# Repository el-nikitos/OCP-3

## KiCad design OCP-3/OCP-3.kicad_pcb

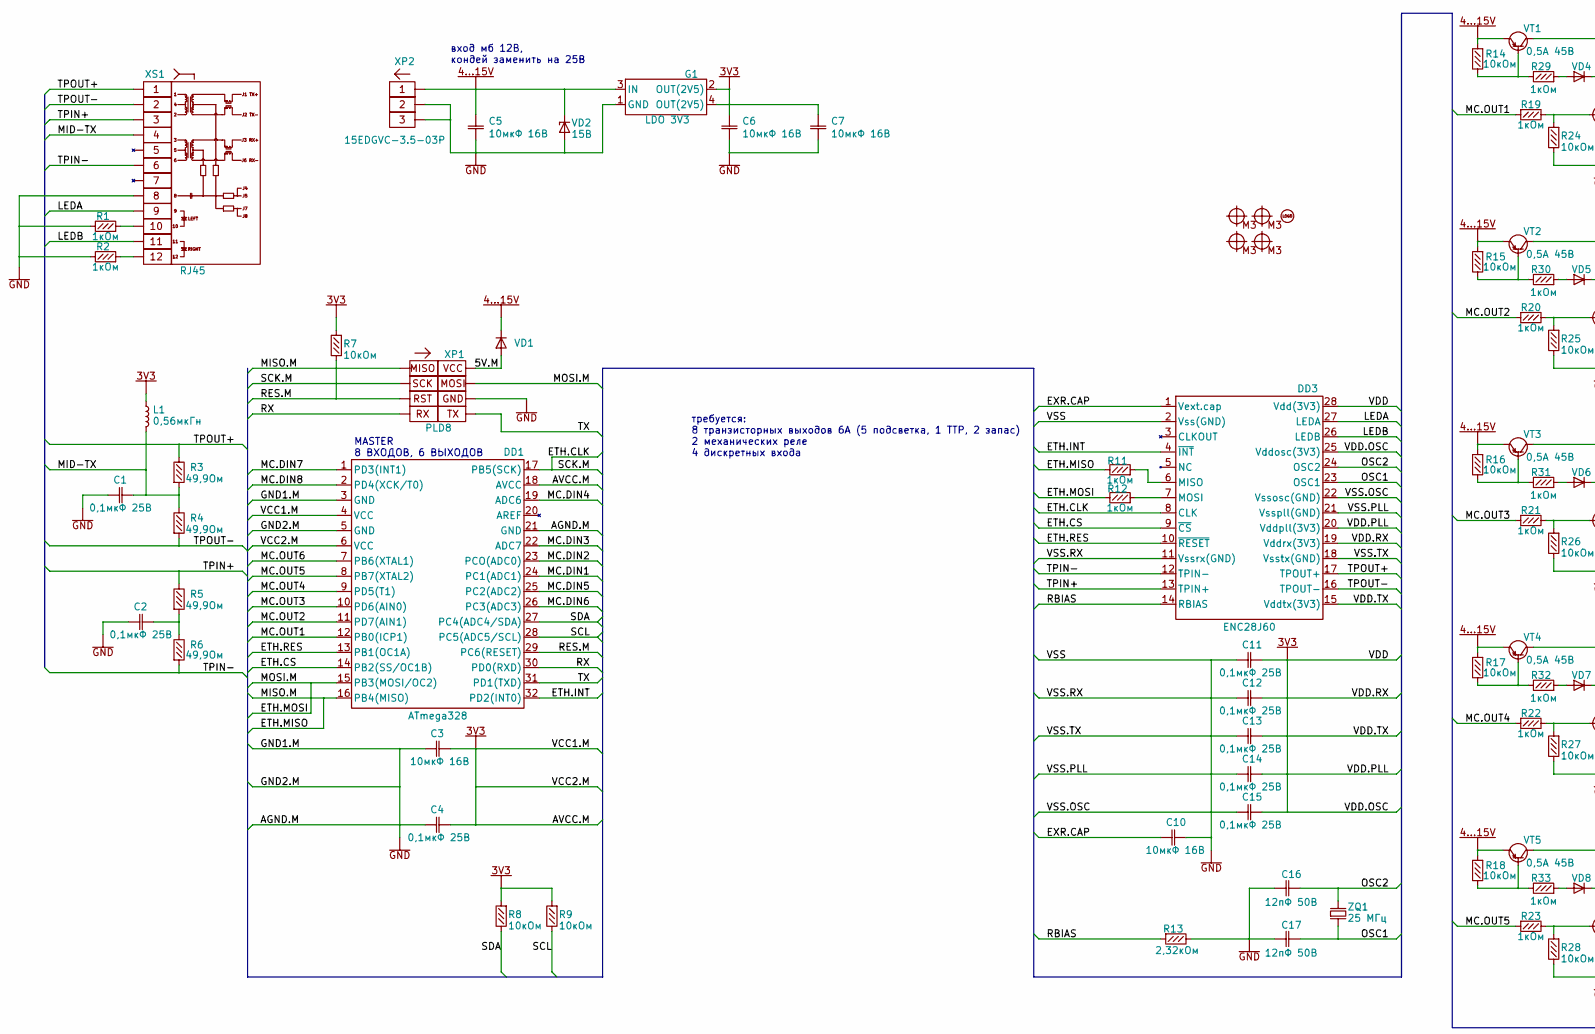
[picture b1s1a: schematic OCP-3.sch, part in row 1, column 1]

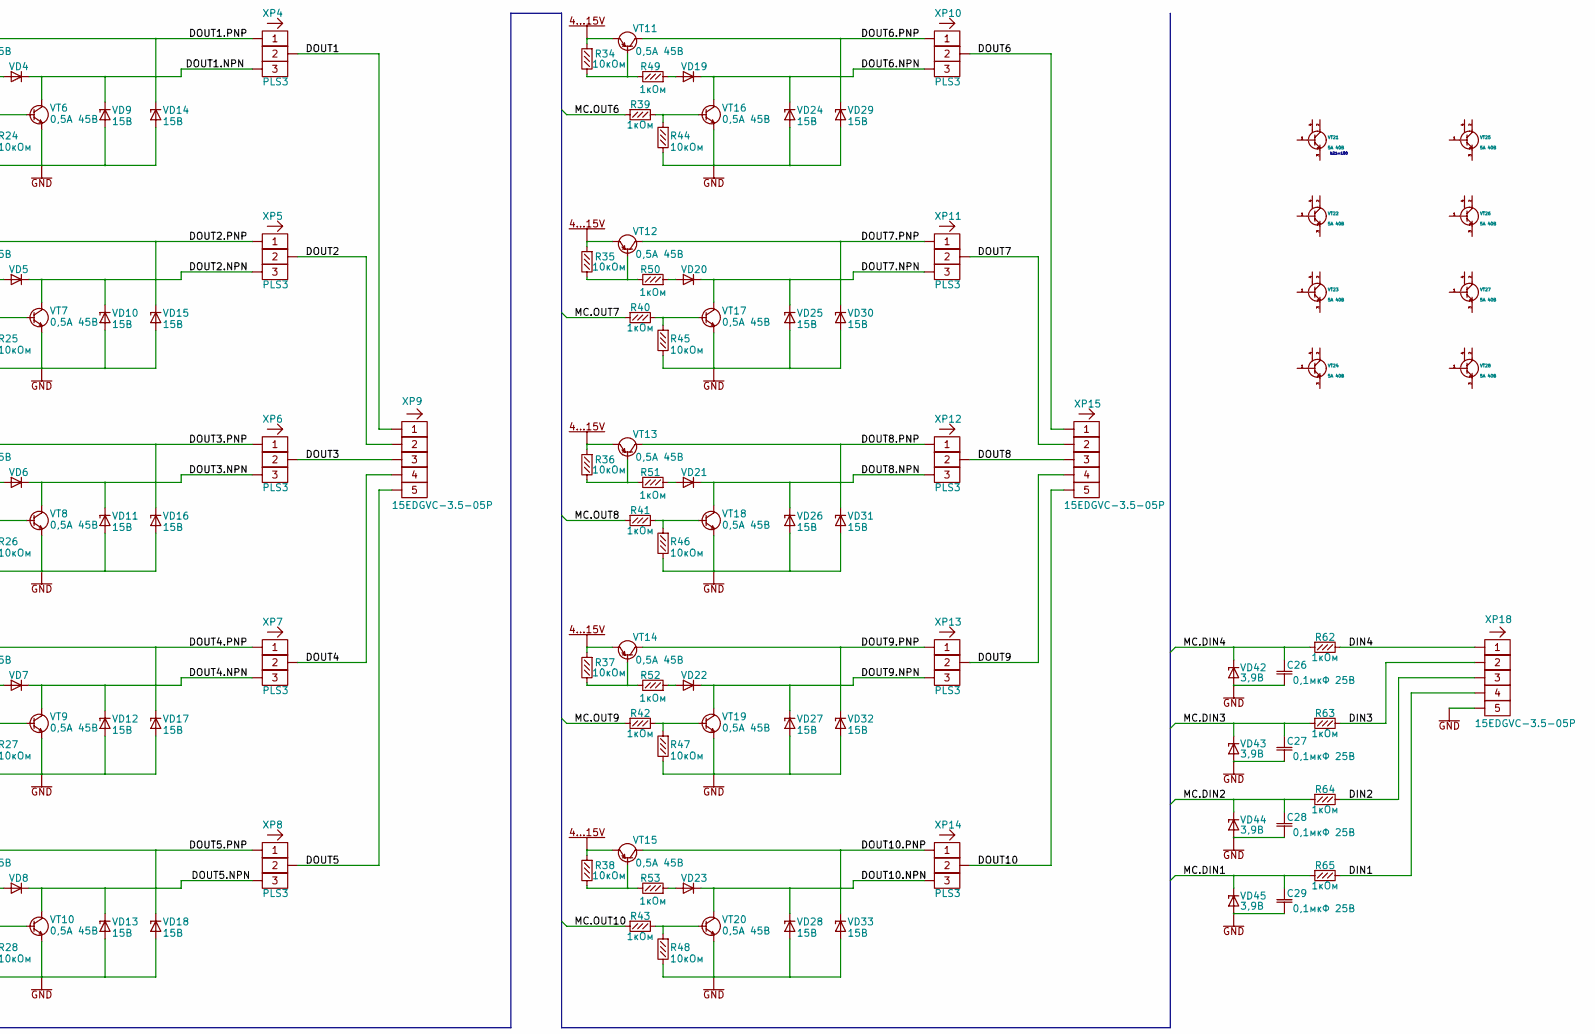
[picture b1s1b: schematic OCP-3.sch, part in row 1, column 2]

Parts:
C1, C2, C4, C11, C12, C13, C14, C15, C26, C27, C28, C29: Конденсатор*0,1мкФ*25В*0603; Конденсатор_SMD_IEC_0603
C3, C5, C6, C7, C10: Конденсатор*10мкФ*16В*0805; Конденсатор_SMD_IEC_0805
C16, C17: Конденсатор*12пФ*50В*0603; Конденсатор_SMD_IEC_0603
DD1: МК*ATmega168*TQFP32; микросхема_ATMEGA-8-161AU
DD3: Преобразователь*ETH-SPI*SSOP28; SSOP-28
G1: LDO*вход_18Вmax*выход_3,3В*ток_1,2АSOT-223; Транзистор_NPN_SOT223_pnp
L1: Чип-индуктивность*0,56мкГн*150мА*0805; Резистор_SMD_IEC_0805_0,125_Вт
R1, R2, R11, R12, R19, R20, R21, R22, R23, R29, R30, R31, R32, R33, R39, R40, R41, R42, R43, R49, R50, R51, R52, R53, R62, R63, R64, R65: Резистор*1кОм*0603; Резистор_SMD_0603_0,065_Вт_pnp
R3, R4, R5, R6: Резистор*49,9кОм*0603; Резистор_SMD_0603_0,065_Вт_pnp
R7, R8, R9, R14, R15, R16, R17, R18, R24, R25, R26, R27, R28, R34, R35, R36, R37, R38, R44, R45, R46, R47, R48: Резистор*10кОм*0603; Резистор_SMD_0603_0,065_Вт_pnp
R13: Резистор*2,32кОм*0603; Резистор_SMD_0603_0,065_Вт_pnp
VD1, VD4, VD5, VD6, VD7, VD8, VD19, VD20, VD21, VD22, VD23: Диод*75В*0,2А*SOD-323; D_SOD-323_HandSoldering
VD2, VD9, VD10, VD11, VD12, VD13, VD14, VD15, VD16, VD17, VD18, VD24, VD25, VD26, VD27, VD28, VD29, VD30, VD31, VD32, VD33: Стабилитрон*15В*SOD80; SOD-80
VD42, VD43, VD44, VD45: Стабилитрон*3,9В*SOD80; SOD-80
VT1, VT2, VT3, VT4, VT5, VT11, VT12, VT13, VT14, VT15: Транзистор*pnp*0,5А*45В*SOT23; Корпус_КТ-46
VT6, VT7, VT8, VT9, VT10, VT16, VT17, VT18, VT19, VT20: Транзистор*npn*0,5А*45В*SOT23; Корпус_КТ-46
VT21, VT22, VT23, VT24, VT25, VT26, VT27, VT28: Транзистор_NPN_1Б-2(4)К-3Э_0; Транзистор_NPN_SOT223
X1, X2, X3, X4: ico*отверстие*М3; Отверстие_М3
X5: ico*LOGO_NIKITOS_10х10; ni_10x10
XP1: Вилка*PLD*8контактов*2ряда*вертикальная*AVR+UART; Вилка_PLD8_вертикальная_AB
XP2: Клеммник*шаг_3,5*3контактов*1ряд*вертикальная; Клеммник_15EDGVC-3.5-03P
XP4, XP5, XP6, XP7, XP8, XP10, XP11, XP12, XP13, XP14: Вилка*PLS*3контактов*1ряд*вертикальная; Вилка_PLS3_вертикальная
XP9, XP15, XP18: Клеммник*шаг_3,5*5контактов*1ряд*вертикальная; Клеммник_15EDGVC-3.5-05P
XS1: Розетка*ETH+трансформатор*8p8c; Розетка_ETH_KLS12-TL002
ZQ1: Резонатор*25МГц*HC-49U; Резонатор_РК456МДУ(DIP)

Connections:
3V3: C3.1, C4.1, C6.1, C7.1, C11.1, C12.1, C13.1, C14.1, C15.1, DD1.4 (VCC), DD1.6 (VCC), DD1.18 (AVCC), DD3.15 (Vddtx(3V3)), DD3.19 (Vddrx(3V3)), DD3.20 (Vddpll(3V3)), DD3.25 (Vddosc(3V3)), DD3.28 (Vdd(3V3)), G1.2 (OUT(2V5)), G1.4 (OUT(2V5)), L1.1, R7.1, R8.1, R9.1
4...15V: C5.1, G1.3 (IN), R14.1, R15.1, R16.1, R17.1, R18.1, R34.1, R35.1, R36.1, R37.1, R38.1, VD1.1, VD2.2, VT1.2, VT2.2, VT3.2, VT4.2, VT5.2, VT11.2, VT12.2, VT13.2, VT14.2, VT15.2, XP2.1
/5V.M: VD1.2, XP1.1B
/DIN1: R65.2, XP18.4
/DIN2: R64.2, XP18.3
/DIN3: R63.2, XP18.2
/DIN4: R62.2, XP18.1
/DOUT1: XP4.2, XP9.1
/DOUT1.NPN: VD4.1, VD9.2, VT6.3, XP4.3
/DOUT1.PNP: VD14.2, VT1.3, XP4.1
/DOUT2: XP5.2, XP9.2
/DOUT2.NPN: VD5.1, VD10.2, VT7.3, XP5.3
/DOUT2.PNP: VD15.2, VT2.3, XP5.1
/DOUT3: XP6.2, XP9.3
/DOUT3.NPN: VD6.1, VD11.2, VT8.3, XP6.3
/DOUT3.PNP: VD16.2, VT3.3, XP6.1
/DOUT4: XP7.2, XP9.4
/DOUT4.NPN: VD7.1, VD12.2, VT9.3, XP7.3
/DOUT4.PNP: VD17.2, VT4.3, XP7.1
/DOUT5: XP8.2, XP9.5
/DOUT5.NPN: VD8.1, VD13.2, VT10.3, XP8.3
/DOUT5.PNP: VD18.2, VT5.3, XP8.1
/DOUT6: XP10.2, XP15.1
/DOUT6.NPN: VD19.1, VD24.2, VT16.3, XP10.3
/DOUT6.PNP: VD29.2, VT11.3, XP10.1
/DOUT7: XP11.2, XP15.2
/DOUT7.NPN: VD20.1, VD25.2, VT17.3, XP11.3
/DOUT7.PNP: VD30.2, VT12.3, XP11.1
/DOUT8: XP12.2, XP15.3
/DOUT8.NPN: VD21.1, VD26.2, VT18.3, XP12.3
/DOUT8.PNP: VD31.2, VT13.3, XP12.1
/DOUT9: XP13.2, XP15.4
/DOUT9.NPN: VD22.1, VD27.2, VT19.3, XP13.3
/DOUT9.PNP: VD32.2, VT14.3, XP13.1
/DOUT10: XP14.2, XP15.5
/DOUT10.NPN: VD23.1, VD28.2, VT20.3, XP14.3
/DOUT10.PNP: VD33.2, VT15.3, XP14.1
/ETH.CLK: DD1.17 (PB5(SCK)), DD3.8 (CLK), XP1.2A
/ETH.CS: DD1.14 (PB2(SS/OC1B)), DD3.9 (~CS)
/ETH.INT: DD1.32 (PD2(INT0)), DD3.4 (~INT)
/ETH.MISO: DD1.16 (PB4(MISO)), R11.2, XP1.1A
/ETH.MOSI: DD1.15 (PB3(MOSI/OC2)), R12.2, XP1.2B
/ETH.RES: DD1.13 (PB1(OC1A)), DD3.10 (~RESET)
/EXR.CAP: C10.2, DD3.1 (Vext.cap)
/LEDA: DD3.27 (LEDA), XS1.9
/LEDB: DD3.26 (LEDB), XS1.11
/MC.DIN1: C29.2, DD1.24 (PC1(ADC1)), R65.1, VD45.2
/MC.DIN2: C28.2, DD1.23 (PCO(ADC0)), R64.1, VD44.2
/MC.DIN3: C27.2, DD1.22 (ADC7), R63.1, VD43.2
/MC.DIN4: C26.2, DD1.19 (ADC6), R62.1, VD42.2
/MC.DIN5: DD1.25 (PC2(ADC2))
/MC.DIN6: DD1.26 (PC3(ADC3))
/MC.DIN7: DD1.1 (PD3(INT1))
/MC.DIN8: DD1.2 (PD4(XCK/T0))
/MC.OUT1: DD1.12 (PB0(ICP1)), R19.1
/MC.OUT2: DD1.11 (PD7(AIN1)), R20.1
/MC.OUT3: DD1.10 (PD6(AIN0)), R21.1
/MC.OUT4: DD1.9 (PD5(T1)), R22.1
/MC.OUT5: DD1.8 (PB7(XTAL2)), R23.1
/MC.OUT6: DD1.7 (PB6(XTAL1)), R39.1
/MC.OUT7: R40.1
/MC.OUT8: R41.1
/MC.OUT9: R42.1
/MC.OUT10: R43.1
/MID-TX: C1.1, L1.2, R3.1, R4.2, XS1.4
/OSC1: C17.1, DD3.23 (OSC1), ZQ1.2
/OSC2: C16.1, DD3.24 (OSC2), ZQ1.1
/RBIAS: DD3.14 (RBIAS), R13.1
/RES.M: DD1.29 (PC6(RESET)), R7.2, XP1.3A
/RX: DD1.30 (PD0(RXD)), XP1.4A
/SCL: DD1.28 (PC5(ADC5/SCL)), R9.2
/SDA: DD1.27 (PC4(ADC4/SDA)), R8.2
/TPIN+: DD3.13 (TPIN+), R5.2, XS1.3
/TPIN-: DD3.12 (TPIN-), R6.1, XS1.6
/TPOUT+: DD3.17 (TPOUT+), R3.2, XS1.1
/TPOUT-: DD3.16 (TPOUT-), R4.1, XS1.2
/TX: DD1.31 (PD1(TXD)), XP1.4B
GND: C1.2, C2.2, C3.2, C4.2, C5.2, C6.2, C7.2, C10.1, C11.2, C12.2, C13.2, C14.2, C15.2, C16.2, C17.2, C26.1, C27.1, C28.1, C29.1, DD1.3 (GND), DD1.5 (GND), DD1.21 (GND), DD3.2 (Vss(GND)), DD3.11 (Vssrx(GND)), DD3.18 (Vsstx(GND)), DD3.21 (Vsspll(GND)), DD3.22 (Vssosc(GND)), G1.1 (GND), R1.2, R2.2, R13.2, R24.2, R25.2, R26.2, R27.2, R28.2, R44.2, R45.2, R46.2, R47.2, R48.2, VD2.1, VD9.1, VD10.1, VD11.1, VD12.1, VD13.1, VD14.1, VD15.1, VD16.1, VD17.1, VD18.1, VD24.1, VD25.1, VD26.1, VD27.1, VD28.1, VD29.1, VD30.1, VD31.1, VD32.1, VD33.1, VD42.1, VD43.1, VD44.1, VD45.1, VT6.2, VT7.2, VT8.2, VT9.2, VT10.2, VT16.2, VT17.2, VT18.2, VT19.2, VT20.2, XP1.3B, XP2.2, XP2.3, XP18.5, XS1.8
unnamed: C2.1, R5.1, R6.2
unnamed: DD3.6 (MISO), R11.1
unnamed: DD3.7 (MOSI), R12.1
unnamed: R1.1, XS1.10
unnamed: R2.1, XS1.12
unnamed: R14.2, R29.2, VT1.1
unnamed: R15.2, R30.2, VT2.1
unnamed: R16.2, R31.2, VT3.1
unnamed: R17.2, R32.2, VT4.1
unnamed: R18.2, R33.2, VT5.1
unnamed: R19.2, R24.1, VT6.1
unnamed: R20.2, R25.1, VT7.1
unnamed: R21.2, R26.1, VT8.1
unnamed: R22.2, R27.1, VT9.1
unnamed: R23.2, R28.1, VT10.1
unnamed: R29.1, VD4.2
unnamed: R30.1, VD5.2
unnamed: R31.1, VD6.2
unnamed: R32.1, VD7.2
unnamed: R33.1, VD8.2
unnamed: R34.2, R49.2, VT11.1
unnamed: R35.2, R50.2, VT12.1
unnamed: R36.2, R51.2, VT13.1
unnamed: R37.2, R52.2, VT14.1
unnamed: R38.2, R53.2, VT15.1
unnamed: R39.2, R44.1, VT16.1
unnamed: R40.2, R45.1, VT17.1
unnamed: R41.2, R46.1, VT18.1
unnamed: R42.2, R47.1, VT19.1
unnamed: R43.2, R48.1, VT20.1
unnamed: R49.1, VD19.2
unnamed: R50.1, VD20.2
unnamed: R51.1, VD21.2
unnamed: R52.1, VD22.2
unnamed: R53.1, VD23.2

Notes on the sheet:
MASTER 8 ВХОДОВ, 6 ВЫХОДОВ
вход мб 12В, кондей заменить на 25В
требуется: 8 транзисторных выходов 6А (5 подсветка, 1 ТТР, 2 запас) 2 механических реле 4 дискретных входа
h21=100

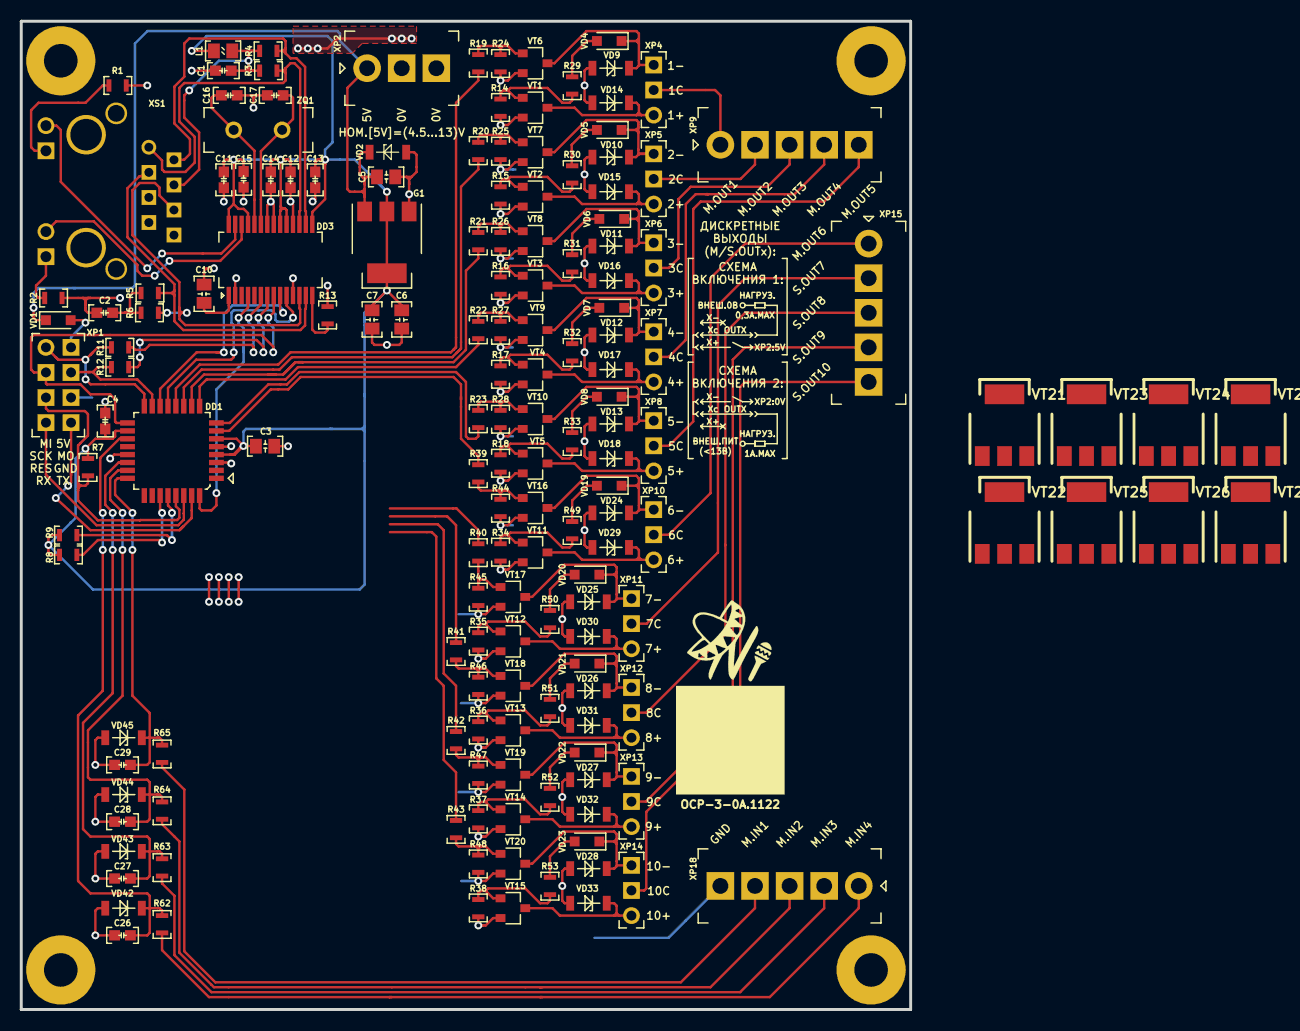
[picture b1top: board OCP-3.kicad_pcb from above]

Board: 2 copper layers, 90.0 x 100.0 mm, 165 parts (0 on the bottom side), 105 nets.

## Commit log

2022-11-14 контроллер умного дома
    проект перенесен из OCP-2
2022-11-14 на схему вынесены транзисторы
